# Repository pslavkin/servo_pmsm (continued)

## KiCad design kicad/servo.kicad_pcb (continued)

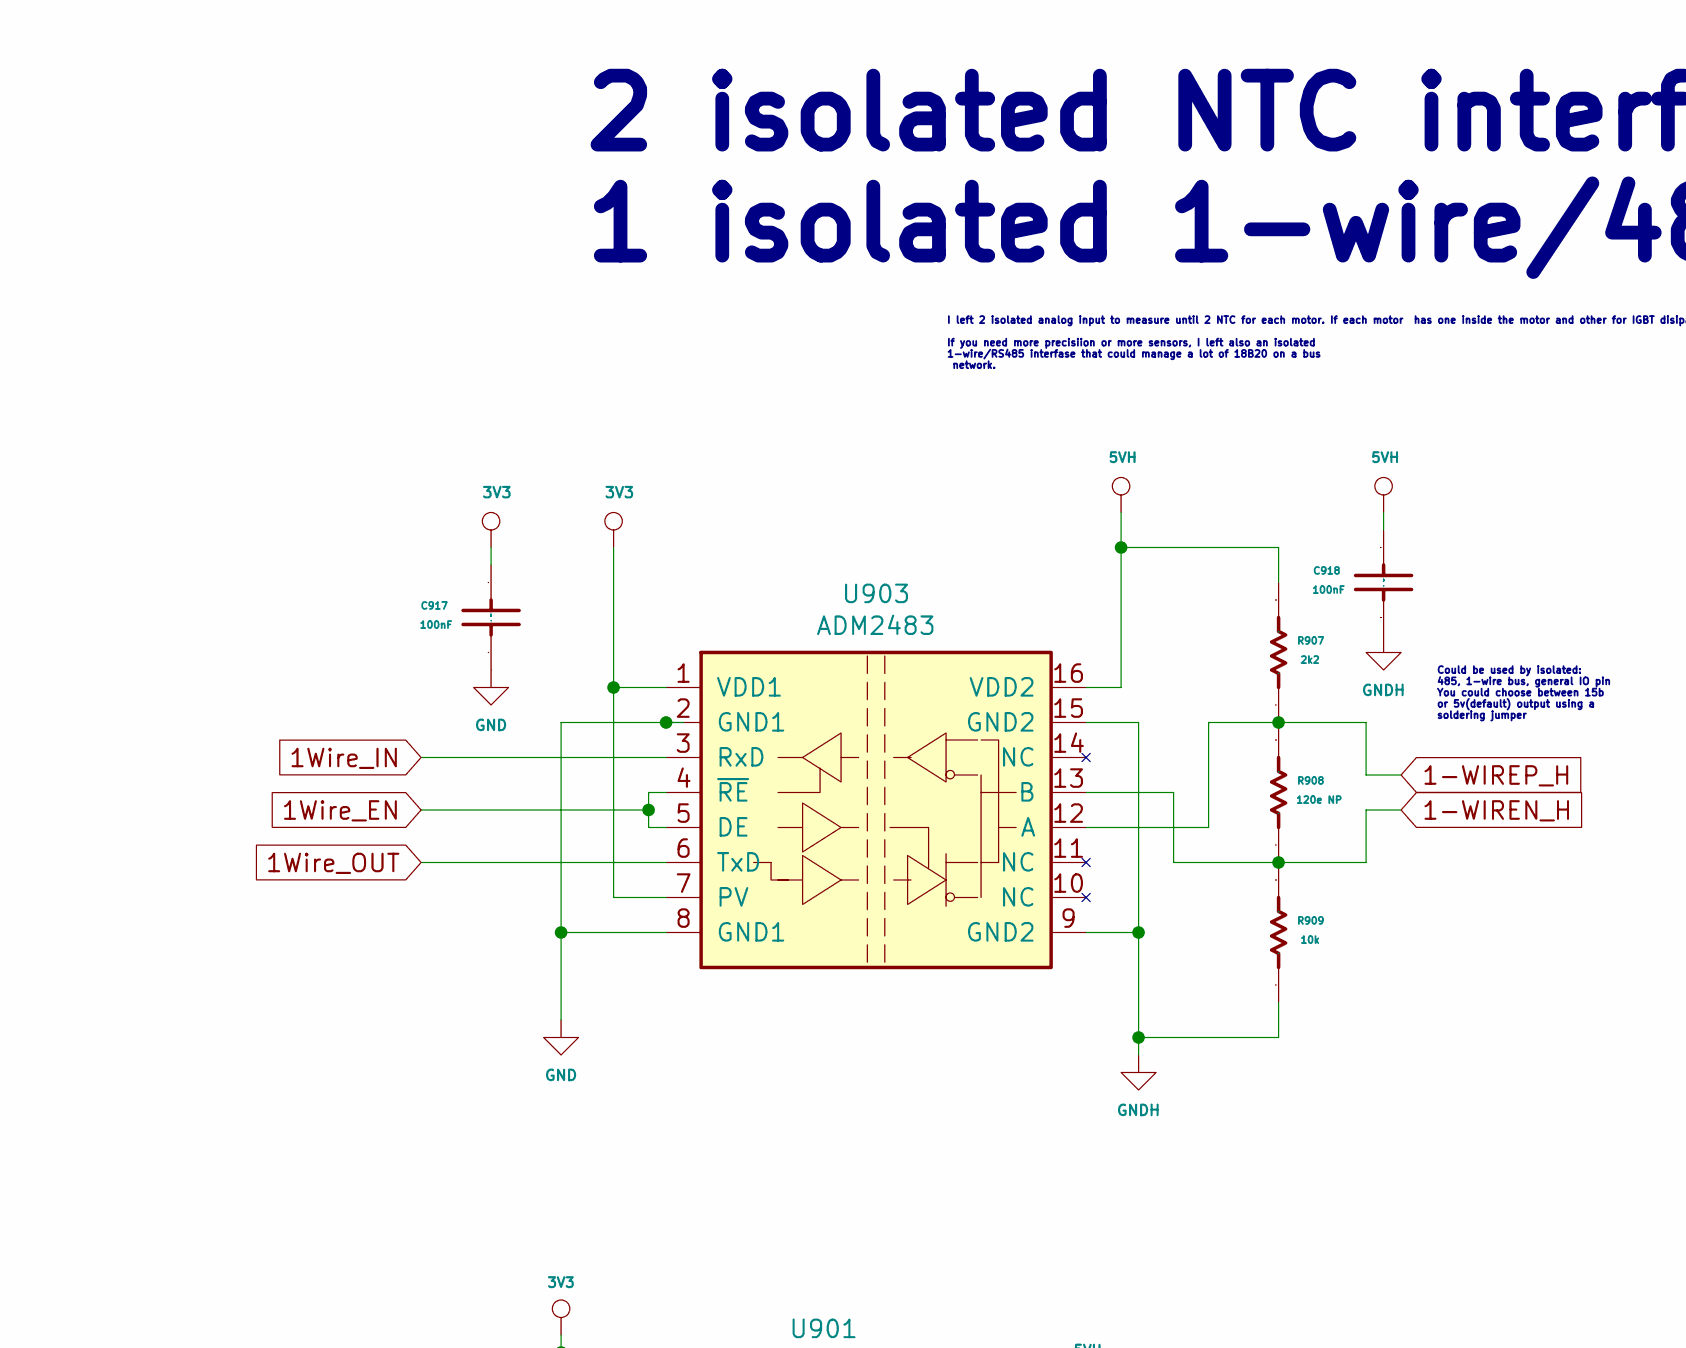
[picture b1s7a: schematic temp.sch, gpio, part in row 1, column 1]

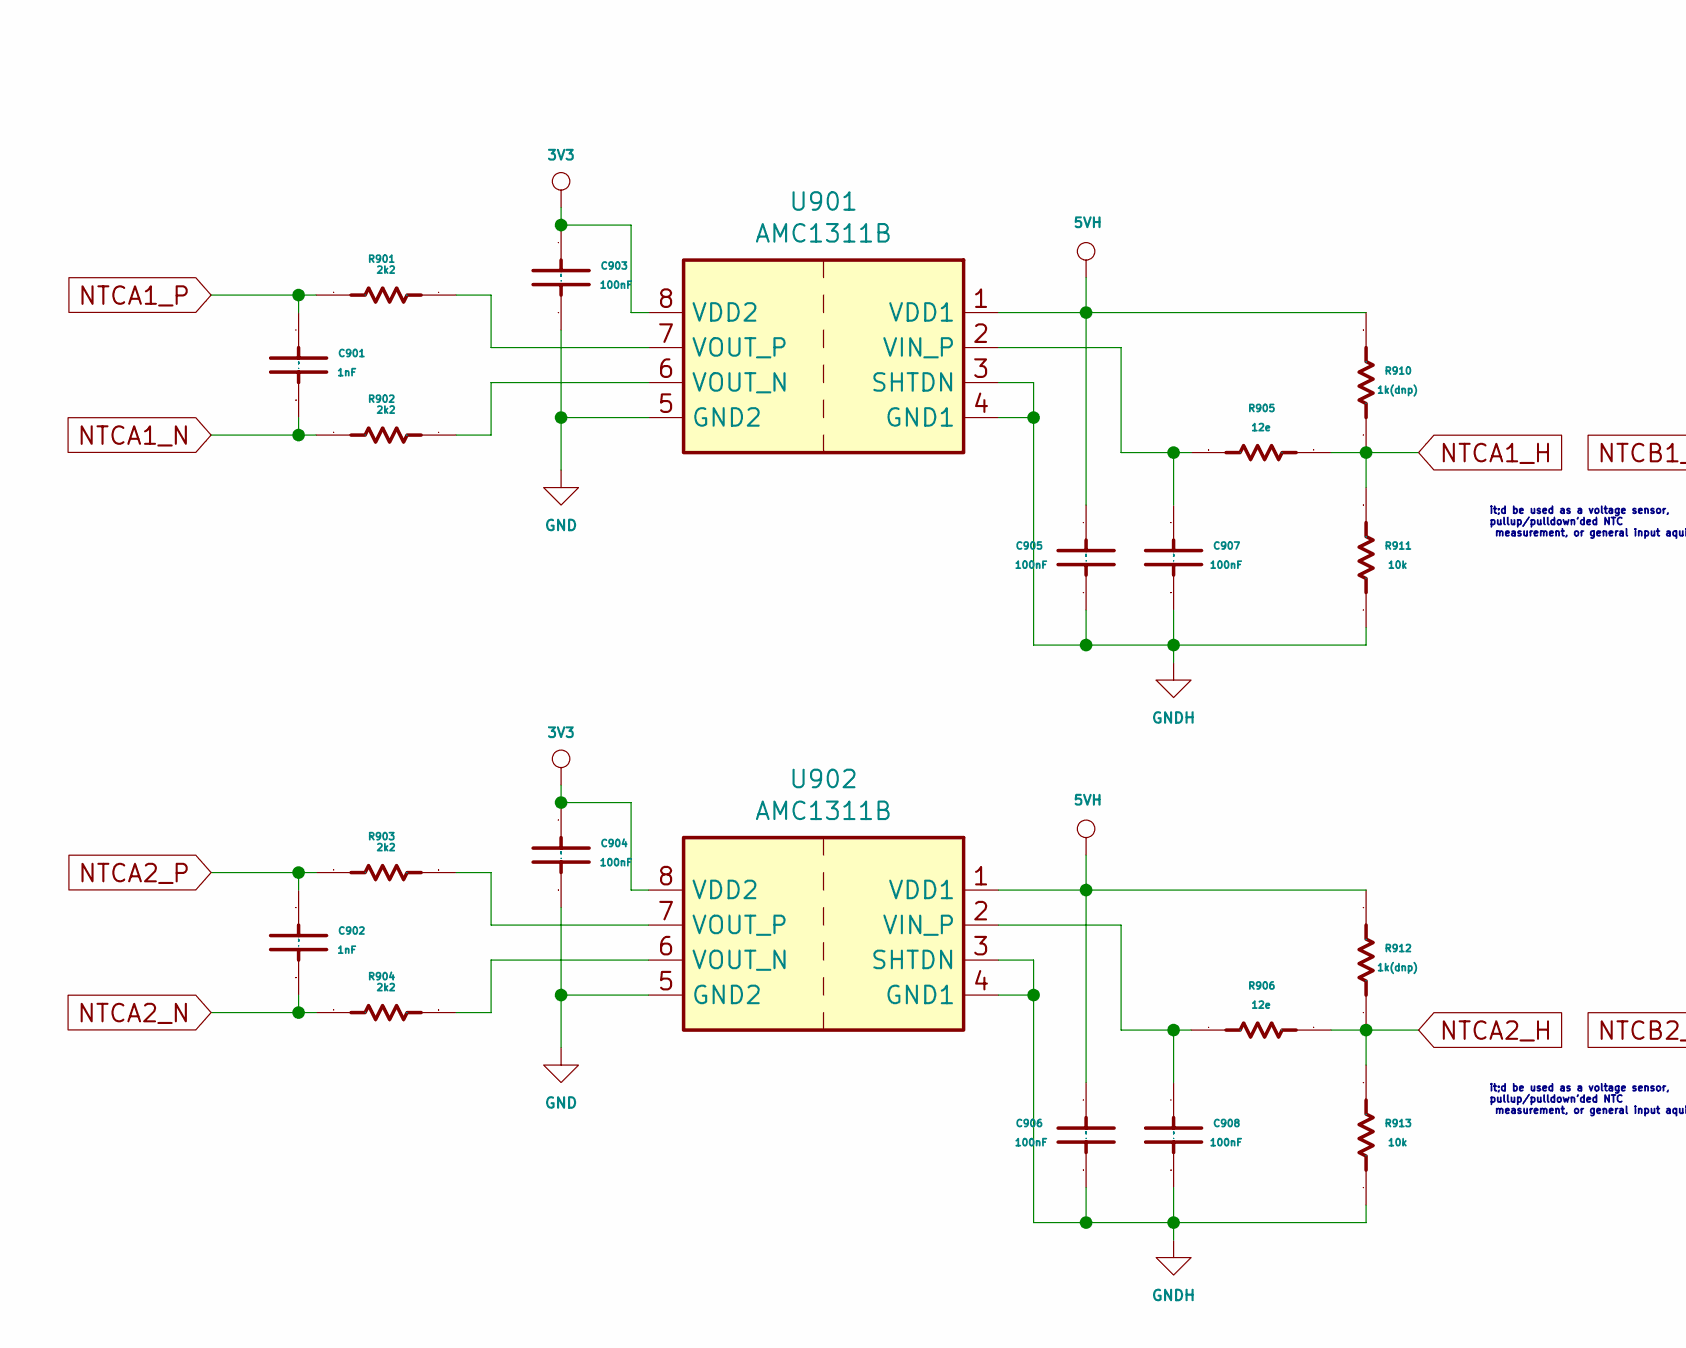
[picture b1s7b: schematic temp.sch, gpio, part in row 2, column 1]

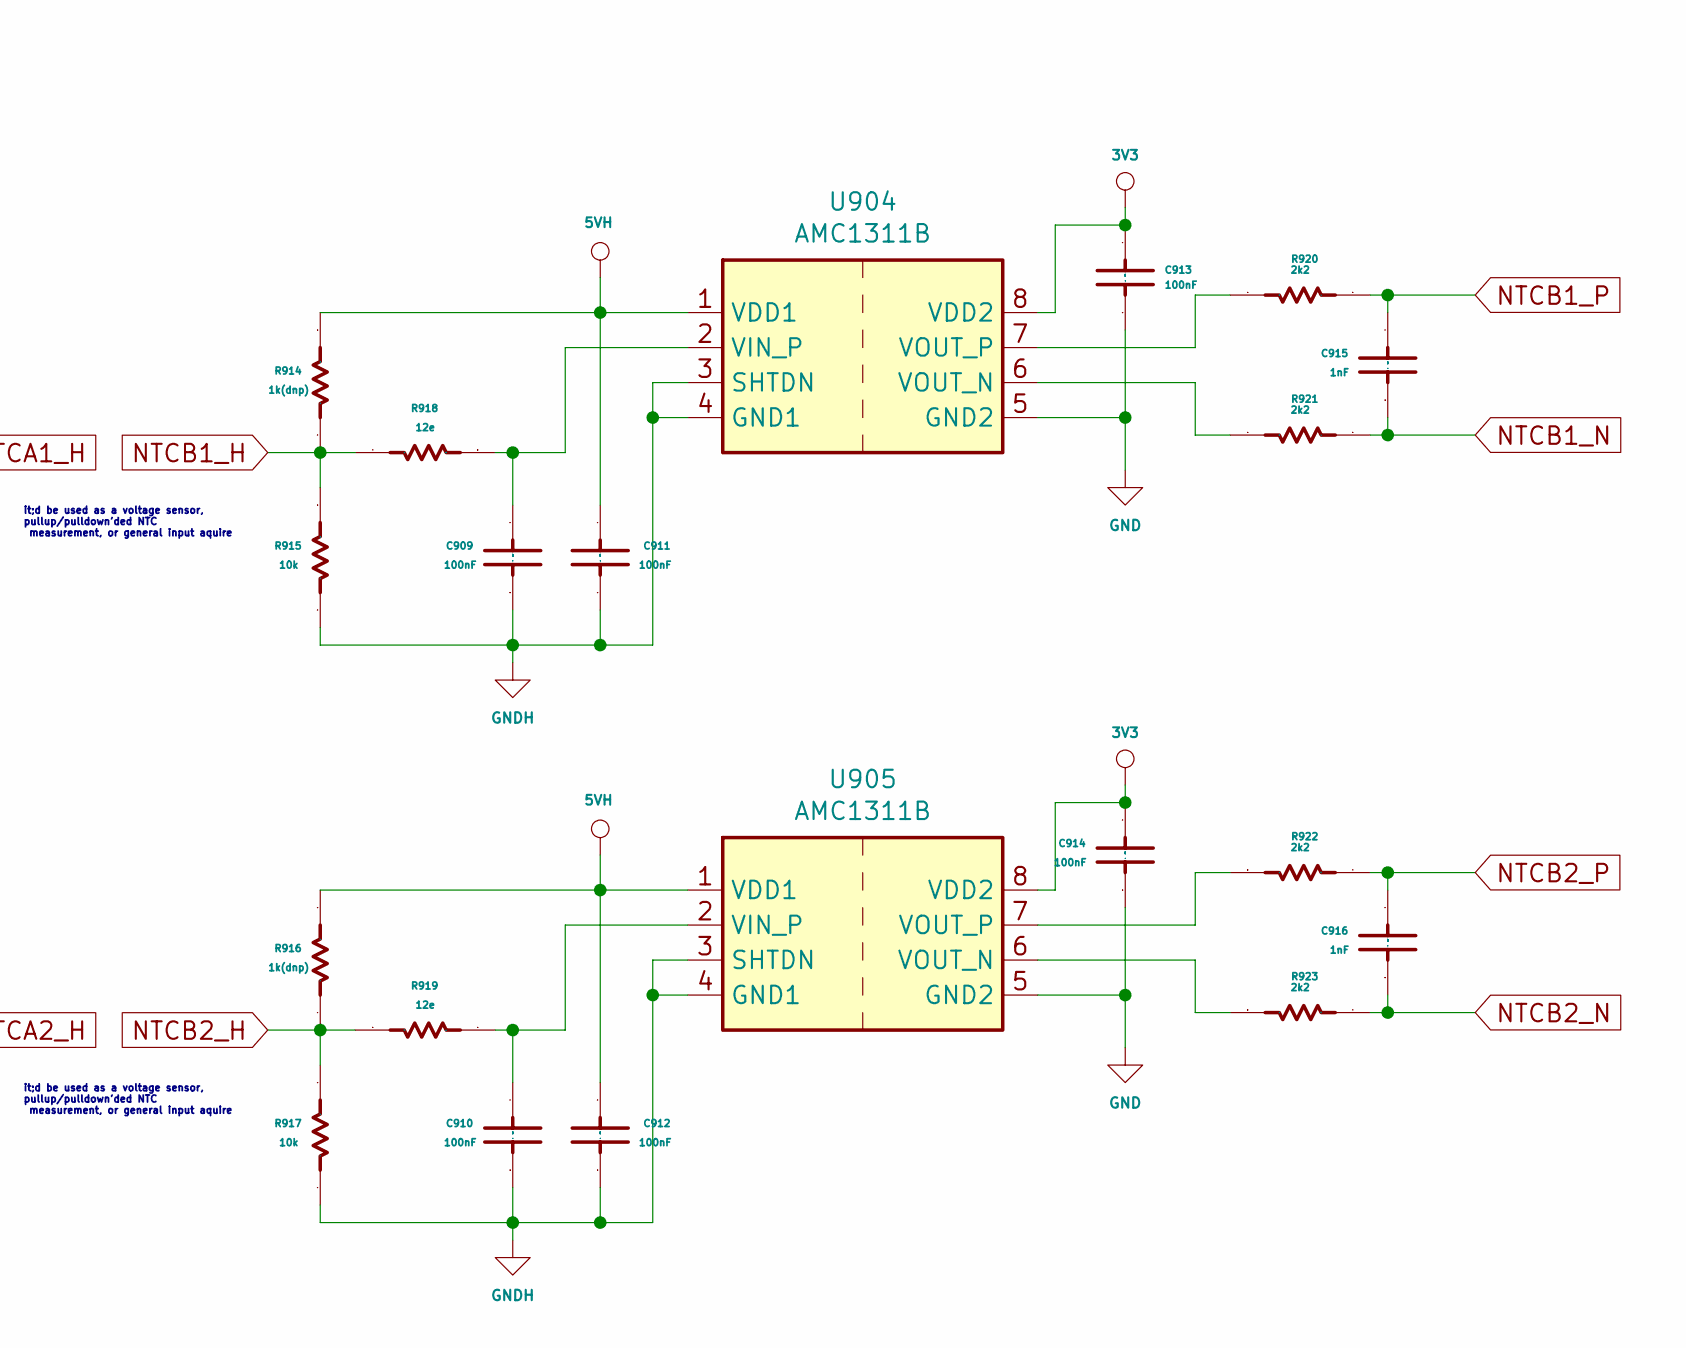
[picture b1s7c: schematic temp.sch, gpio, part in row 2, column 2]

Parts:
C901, C902, C915, C916: 1nF; C_0603_1608Metric
C903, C904, C905, C906, C907, C908, C909, C910, C911, C912, C913, C914, C917, C918: 100nF; C_0603_1608Metric
R901, R902, R903, R904, R907, R920, R921, R922, R923: 2k2; R_0603_1608Metric
R905, R906, R918, R919: 12e; R_0603_1608Metric
R908: 120e NP; R_0603_1608Metric
R909, R911, R913, R915, R917: 10k; R_0603_1608Metric
R910, R912, R914, R916: 1k(dnp); R_0603_1608Metric
U901, U902, U904, U905: AMC1311B; SSO-8_9.6x6.3mm_P1.27mm_Clearance10.5mm
U903: ADM2483; SOIC-16W_7.5x10.3mm_P1.27mm

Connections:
1-WIREN_H: R908.2, R909.1, U903.13 (B); also elsewhere on the board
1-WIREP_H: R907.2, R908.1, U903.12 (A); also elsewhere on the board
1Wire_EN: U903.4 (~RE), U903.5 (DE); also elsewhere on the board
1Wire_IN: U903.3 (RxD); also elsewhere on the board
1Wire_OUT: U903.6 (TxD); also elsewhere on the board
3V3: C903.2 (Capacitor), C904.2 (Capacitor), C913.2 (Capacitor), C914.2 (Capacitor), C917.2 (Capacitor), U901.8 (VDD2), U902.8 (VDD2), U903.1 (VDD1), U903.7 (PV), U904.8 (VDD2), U905.8 (VDD2); also elsewhere on the board
5VH: C905.2 (Capacitor), C906.2 (Capacitor), C911.2 (Capacitor), C912.2 (Capacitor), C918.2 (Capacitor), R907.1, R910.1, R912.1, R914.1, R916.1, U901.1 (VDD1), U902.1 (VDD1), U903.16 (VDD2), U904.1 (VDD1), U905.1 (VDD1); also elsewhere on the board
GND: C903.1, C904.1, C913.1, C914.1, C917.1, U901.5 (GND2), U902.5 (GND2), U903.2 (GND1), U903.8 (GND1), U904.5 (GND2), U905.5 (GND2); also elsewhere on the board
GNDH: C905.1, C906.1, C907.1, C908.1, C909.1, C910.1, C911.1, C912.1, C918.1, R909.2, R911.2, R913.2, R915.2, R917.2, U901.3 (SHTDN), U901.4 (GND1), U902.3 (SHTDN), U902.4 (GND1), U903.9 (GND2), U903.15 (GND2), U904.3 (SHTDN), U904.4 (GND1), U905.3 (SHTDN), U905.4 (GND1); also elsewhere on the board
NTCA1_H: R905.2, R910.2, R911.1; also elsewhere on the board
NTCA1_N: C901.1, R902.2; also elsewhere on the board
NTCA1_P: C901.2 (Capacitor), R901.2; also elsewhere on the board
NTCA2_H: R906.2, R912.2, R913.1; also elsewhere on the board
NTCA2_N: C902.1, R904.2; also elsewhere on the board
NTCA2_P: C902.2 (Capacitor), R903.2; also elsewhere on the board
NTCB1_H: R914.2, R915.1, R918.2; also elsewhere on the board
NTCB1_N: C915.1, R921.2; also elsewhere on the board
NTCB1_P: C915.2 (Capacitor), R920.2; also elsewhere on the board
NTCB2_H: R916.2, R917.1, R919.2; also elsewhere on the board
NTCB2_N: C916.1, R923.2; also elsewhere on the board
NTCB2_P: C916.2 (Capacitor), R922.2; also elsewhere on the board
unnamed: C907.2 (Capacitor), R905.1, U901.2 (VIN_P)
unnamed: C908.2 (Capacitor), R906.1, U902.2 (VIN_P)
unnamed: C909.2 (Capacitor), R918.1, U904.2 (VIN_P)
unnamed: C910.2 (Capacitor), R919.1, U905.2 (VIN_P)
unnamed: R901.1, U901.7 (VOUT_P)
unnamed: R902.1, U901.6 (VOUT_N)
unnamed: R903.1, U902.7 (VOUT_P)
unnamed: R904.1, U902.6 (VOUT_N)
unnamed: R920.1, U904.7 (VOUT_P)
unnamed: R921.1, U904.6 (VOUT_N)
unnamed: R922.1, U905.7 (VOUT_P)
unnamed: R923.1, U905.6 (VOUT_N)

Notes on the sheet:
Could be used by isolated: 485, 1-wire bus, general IO pin You could choose between 15b or 5v(default) output using a soldering jumper
2 isolated NTC interfase + 1 isolated 1-wire/485
it;d be used as a voltage sensor, pullup/pulldown'ded NTC measurement, or general input aquire
I left 2 isolated analog input to measure until 2 NTC for each motor. If each motor has one inside the motor and other for IGBT disipator, If you need more precisiion or more sensors, I left also an isolated 1-wire/RS485 interfase that could manage a lot of 18B20 on a bus network.

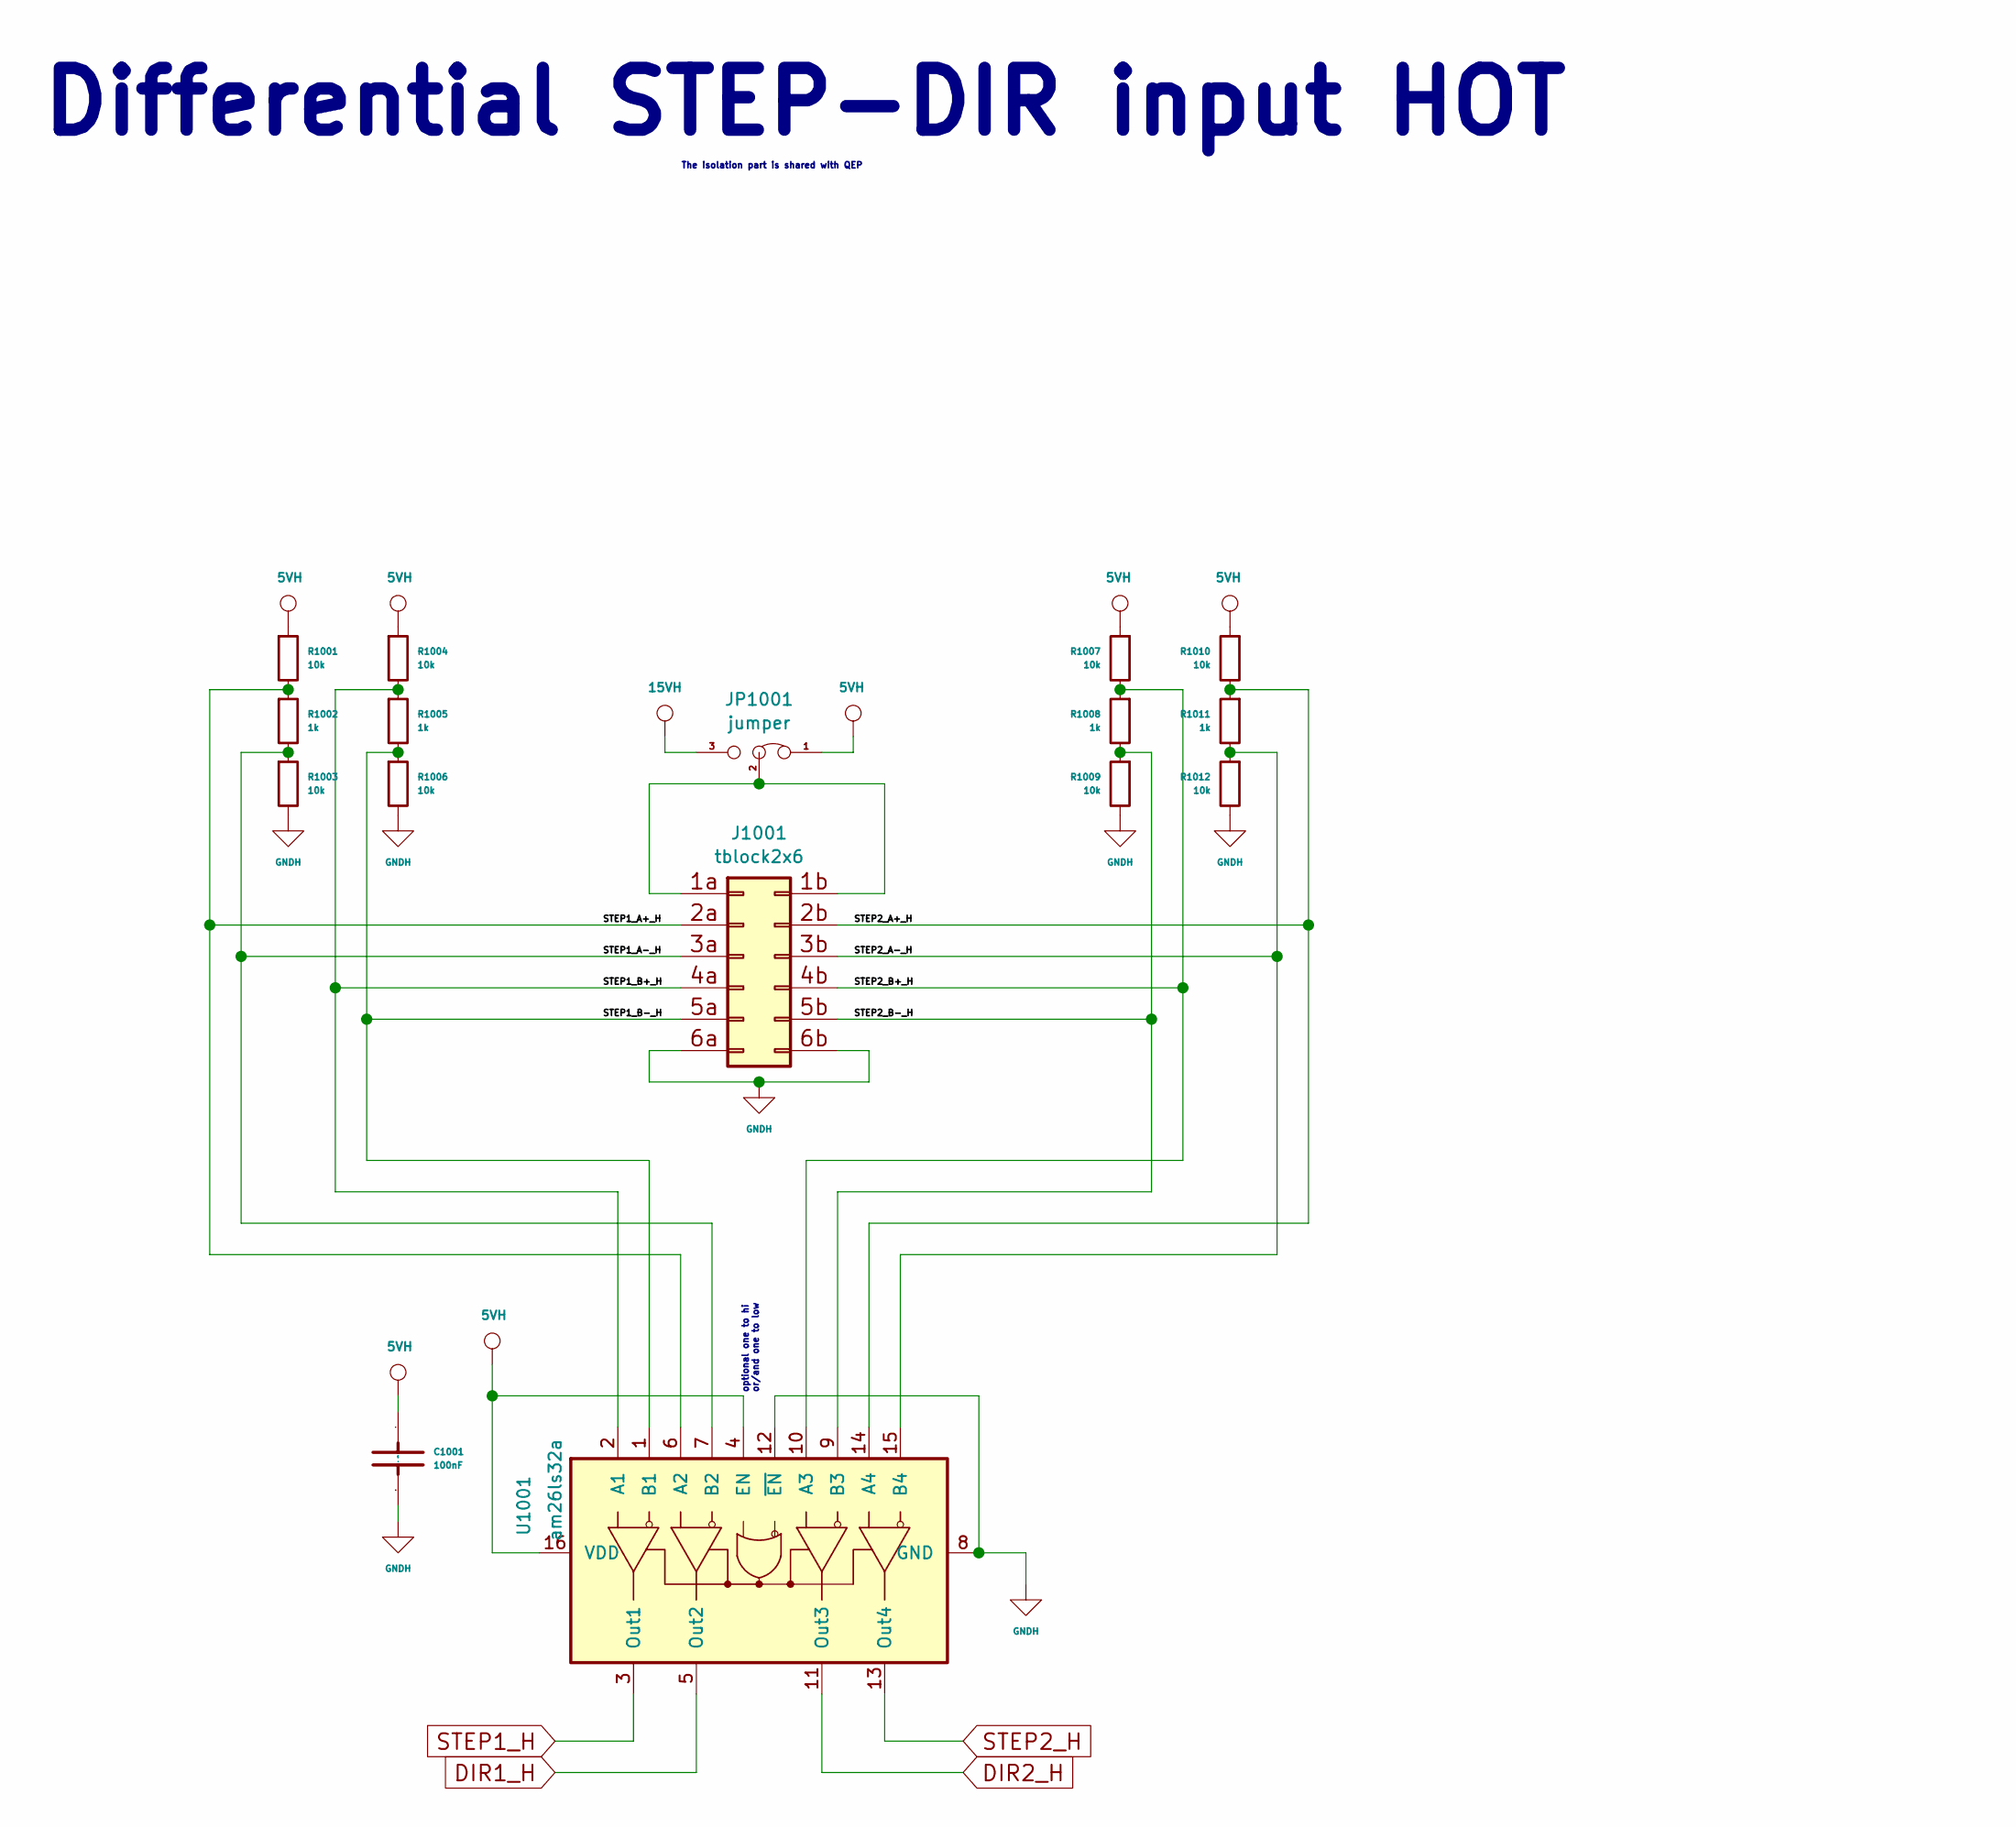
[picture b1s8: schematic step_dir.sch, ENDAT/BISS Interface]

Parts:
C1001: 100nF; C_0603_1608Metric
J1001: tblock2x6; tblock02x6_3.81
JP1001: jumper; SolderJumper-3_P1.3mm_Open_RoundedPad1.0x1.5mm
R1001, R1003, R1004, R1006, R1007, R1009, R1010, R1012: 10k; R_0603_1608Metric
R1002, R1005, R1008, R1011: 1k; R_0603_1608Metric
U1001: am26ls32a; SOIC-16W_5.3x10.2mm_P1.27mm

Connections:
5VH: C1001.2 (Capacitor), JP1001.1 (A), R1001.1, R1004.1, R1007.1, R1010.1, U1001.4 (EN), U1001.16 (VDD); also elsewhere on the board
15VH: JP1001.3 (B); also elsewhere on the board
/step_dir/STEP1_A+_H: J1001.2a, R1001.2, R1002.1, U1001.6 (A2)
/step_dir/STEP1_A-_H: J1001.3a, R1002.2, R1003.1, U1001.7 (B2)
/step_dir/STEP1_B+_H: J1001.4a, R1004.2, R1005.1, U1001.2 (A1)
/step_dir/STEP1_B-_H: J1001.5a, R1005.2, R1006.1, U1001.1 (B1)
/step_dir/STEP2_A+_H: J1001.2b, R1010.2, R1011.1, U1001.14 (A4)
/step_dir/STEP2_A-_H: J1001.3b, R1011.2, R1012.1, U1001.15 (B4)
/step_dir/STEP2_B+_H: J1001.4b, R1007.2, R1008.1, U1001.10 (A3)
/step_dir/STEP2_B-_H: J1001.5b, R1008.2, R1009.1, U1001.9 (B3)
DIR1_H: U1001.5 (Out2); also elsewhere on the board
DIR2_H: U1001.11 (Out3); also elsewhere on the board
GNDH: C1001.1, J1001.6a, J1001.6b, R1003.2, R1006.2, R1009.2, R1012.2, U1001.8 (GND), U1001.12 (~EN); also elsewhere on the board
unnamed: J1001.1a, J1001.1b, JP1001.2 (C)
STEP1_H: U1001.3 (Out1); also elsewhere on the board
STEP2_H: U1001.13 (Out4); also elsewhere on the board

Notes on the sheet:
Differential STEP-DIR input HOT
optional one to hi or/and one to low
The isolation part is shared with QEP

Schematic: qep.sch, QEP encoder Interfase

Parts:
C1101, C1102, C1103, C1104, C1105, C1106: 100nF; C_0603_1608Metric
J1101: tblock; tblock02x10_3.81
JP1101: jumper; SolderJumper-3_P1.3mm_Open_RoundedPad1.0x1.5mm
R1101, R1103, R1104, R1106, R1107, R1109, R1110, R1112, R1113, R1115, R1116, R1118, R1119, R1121, R1122, R1124: 10k; R_0603_1608Metric
R1102, R1105, R1108, R1111, R1114, R1117, R1120, R1123: 1k; R_0603_1608Metric
U1101, U1104: SI8660BD; SOIC-16W_7.5x10.3mm_P1.27mm
U1102, U1103: am26ls32a; SOIC-16W_5.3x10.2mm_P1.27mm

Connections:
3V3: C1101.2 (Capacitor), C1106.2 (Capacitor), U1101.16 (VCC2), U1104.16 (VCC2); also elsewhere on the board
5VH: C1102.2 (Capacitor), C1103.2 (Capacitor), C1104.2 (Capacitor), C1105.2 (Capacitor), JP1101.1 (A), R1101.1, R1104.1, R1107.1, R1110.1, R1113.1, R1116.1, R1119.1, R1122.1, U1101.1 (VCC1), U1102.4 (EN), U1102.16 (VDD), U1103.4 (EN), U1103.16 (VDD), U1104.1 (VCC1); also elsewhere on the board
15VH: JP1101.3 (B); also elsewhere on the board
/qep/QEP1_A+_H: J1101.2a, R1101.2, R1102.1, U1102.2 (A1)
/qep/QEP1_A-_H: J1101.3a, R1102.2, R1103.1, U1102.1 (B1)
/qep/QEP1_B+_H: J1101.4a, R1104.2, R1105.1, U1102.6 (A2)
/qep/QEP1_B-_H: J1101.5a, R1105.2, R1106.1, U1102.7 (B2)
/qep/QEP1_I+_H: J1101.6a, R1107.2, R1108.1, U1102.10 (A3)
/qep/QEP1_I-_H: J1101.7a, R1108.2, R1109.1, U1102.9 (B3)
/qep/QEP1_S+_H: J1101.8a, R1110.2, R1111.1, U1102.14 (A4)
/qep/QEP1_S-_H: J1101.9a, R1111.2, R1112.1, U1102.15 (B4)
/qep/QEP2_A+_H: J1101.2b, R1122.2, R1123.1, U1103.2 (A1)
/qep/QEP2_A-_H: J1101.3b, R1123.2, R1124.1, U1103.1 (B1)
/qep/QEP2_B+_H: J1101.4b, R1119.2, R1120.1, U1103.6 (A2)
/qep/QEP2_B-_H: J1101.5b, R1120.2, R1121.1, U1103.7 (B2)
/qep/QEP2_I+_H: J1101.6b, R1116.2, R1117.1, U1103.10 (A3)
/qep/QEP2_I-_H: J1101.7b, R1117.2, R1118.1, U1103.9 (B3)
/qep/QEP2_S+_H: J1101.8b, R1113.2, R1114.1, U1103.14 (A4)
/qep/QEP2_S-_H: J1101.9b, R1114.2, R1115.1, U1103.15 (B4)
DIR1: U1101.10 (B6); also elsewhere on the board
DIR1_H: U1101.7 (A6); also elsewhere on the board
DIR2: U1104.10 (B6); also elsewhere on the board
DIR2_H: U1104.7 (A6); also elsewhere on the board
GND: C1101.1, C1106.1, U1101.9 (GND2), U1104.9 (GND2); also elsewhere on the board
GNDH: C1102.1, C1103.1, C1104.1, C1105.1, J1101.10a, J1101.10b, R1103.2, R1106.2, R1109.2, R1112.2, R1115.2, R1118.2, R1121.2, R1124.2, U1101.8 (GND1), U1102.8 (GND), U1102.12 (~EN), U1103.8 (GND), U1103.12 (~EN), U1104.8 (GND1); also elsewhere on the board
unnamed: J1101.1a, J1101.1b, JP1101.2 (C)
unnamed: U1101.2 (A1), U1102.3 (Out1)
unnamed: U1101.3 (A2), U1102.5 (Out2)
unnamed: U1101.4 (A3), U1102.11 (Out3)
unnamed: U1101.5 (A4), U1102.13 (Out4)
unnamed: U1103.3 (Out1), U1104.2 (A1)
unnamed: U1103.5 (Out2), U1104.3 (A2)
unnamed: U1103.11 (Out3), U1104.4 (A3)
unnamed: U1103.13 (Out4), U1104.5 (A4)
QEP1_A: U1101.15 (B1); also elsewhere on the board
QEP1_B: U1101.14 (B2); also elsewhere on the board
QEP1_I: U1101.13 (B3); also elsewhere on the board
QEP1_S: U1101.12 (B4); also elsewhere on the board
QEP2_A: U1104.15 (B1); also elsewhere on the board
QEP2_B: U1104.14 (B2); also elsewhere on the board
QEP2_I: U1104.13 (B3); also elsewhere on the board
QEP2_S: U1104.12 (B4); also elsewhere on the board
STEP1: U1101.11 (B5); also elsewhere on the board
STEP1_H: U1101.6 (A5); also elsewhere on the board
STEP2: U1104.11 (B5); also elsewhere on the board
STEP2_H: U1104.6 (A5); also elsewhere on the board

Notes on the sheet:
2x Isolated Idifferential ncremental encoder interfase 5v input A-B-I-S
I left the input for two isolated incremental encoders. I left the 4 signals input plus two auxiliary output for eny porpous plus the ability to choose between 5 or 15vH
optional one to hi or/and one to low
Choose a package pin-to-pin compatible with TI ISO7760. But SIlabs cost halt the price as TI

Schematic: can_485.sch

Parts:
C1201, C1202, C1203, C1204: 100nF; C_0603_1608Metric
J1201: tblock2x4; tblock02x4_3.81
JP1201, JP1202: jumper; SolderJumper-3_P1.3mm_Open_RoundedPad1.0x1.5mm
R1201, R1203, R1204, R1206: 10k; R_0603_1608Metric
R1202, R1205: 1k; R_0603_1608Metric
U1201: ISO1050; SSO-8_6.7x9.8mm_P2.54mm_Clearance8mm
U1202: ADM2483; SOIC-16W_7.5x10.3mm_P1.27mm

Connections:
3V3: C1201.2 (Capacitor), C1204.2 (Capacitor), U1201.1 (VCC1), U1202.1 (VDD1), U1202.7 (PV); also elsewhere on the board
5VH: C1202.2 (Capacitor), C1203.2 (Capacitor), JP1201.1 (A), R1201.1, R1204.1, U1201.8 (VCC2), U1202.16 (VDD2); also elsewhere on the board
15VH: JP1201.3 (B); also elsewhere on the board
CAN_RX: U1201.2 (RxD); also elsewhere on the board
CAN_TX: U1201.3 (TxD); also elsewhere on the board
Earth: JP1202.1 (A); also elsewhere on the board
GND: C1201.1, C1204.1, U1201.4 (GND1), U1202.2 (GND1), U1202.8 (GND1); also elsewhere on the board
GNDH: C1202.1, C1203.1, JP1202.3 (B), R1203.2, R1206.2, U1201.5 (GND2), U1202.9 (GND2), U1202.15 (GND2); also elsewhere on the board
unnamed: J1201.1a, J1201.1b, JP1201.2 (C)
unnamed: J1201.2a, R1201.2, R1202.1, U1201.7 (CANH)
unnamed: J1201.2b, R1204.2, R1205.1, U1202.12 (A)
unnamed: J1201.3a, R1202.2, R1203.1, U1201.6 (CANL)
unnamed: J1201.3b, R1205.2, R1206.1, U1202.13 (B)
unnamed: J1201.4a, J1201.4b, JP1202.2 (C)
RS485_EN: U1202.4 (~RE), U1202.5 (DE); also elsewhere on the board
RS485_RX: U1202.3 (RxD); also elsewhere on the board
RS485_TX: U1202.6 (TxD); also elsewhere on the board

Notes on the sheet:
Isolated CAN interfase
A simple CAN driver. It also could be used as a RS485 driver in his speed.. the minimum for CAN is 40kbos, so in RS485 at 9600 could be fine
Could be used by isolated: 485, 1-wire bus, general IO pin
Isolated RS485
With these interfase you could manage isolated RS485 or isolated GPIO or isolated 1-Wire, using 5H or 15H as a supply

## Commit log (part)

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2019-07-05 biginig. do comppile, do run on cpi, all code on git
    I spend a couple of days understunding the c2000 driverlib arquitecture
    to manage my own project workspace all incluede. I only depends on the
    compiler, but the fp32.lib, and driverlib codes, and header are all
    inside the gir, so I'd change everythins and move the project from PC
    without looss codes.. let go!
2019-07-05 blow up 'cose project name change. Solved -> servo_pmsm
2019-07-06 cbuffers into scia. as a module, so I'd use cbuffer for events
2019-07-06 leds up! lets ticl begore the parser...
    I've added some files to git, that I'd forget from last commit.. leds
    are running and ready to use. I'm planning the tick begore parsser..
2019-07-07 systick with flag UP!, the problem is related to isr chained
    I remove the enable/disable isr for timer2 when in smachine and the
    problem of jitter goes. It seems that timer2 doesn't like it. I decided
    for now add at the end of sm a systick function that pool a flag that
    timer2 isr set. So I don't need to disable/enable irqs to read the
    events, 'cose til now the event writes are done allways in user mode,
    not isr.. but it could change latter..
2019-07-08 uptime print UP!, just to test the cmdlineProcces
    I've added a simple clock to check the uptime and see if the systems got
    hangs suddenly... keep working
2019-07-09 ADC UP! using SOC and software trigger 12bits single ended
    I've manage to put adc to work configurin 12bits using soc0 and testing
    irq flag to test completion. It's basic but working example integrated
    ti the rtos and cmdline to sample using sci and keyboard, si it's ready
    to modify, go on...
2019-07-11 keep doing README adding requisites
2019-07-11 added gif video demo for sci test and some updates in README
2019-07-11 test scaled gif for readable solution
2019-07-13 add iqmath lib for eqep.c calculations. Also change cmd's
    I've added eqep, but it need iqmath lib, so I'd to add thouse .libs and
    .h include files to manage that. Not Debug and Release versions works, o
    at least compile and don't hang. Now it's time to test eqep output..
    lets go
2019-07-14 EQEP at 50kedges/sec works. Maybe it's hardware limitation
    I'm measuring speed of 50kedges/sec max. I guess the pulse deformation
    and the 5v<->3v translator limitation could distor the pulses. I'll
    measure next by osc. For now it's enought to continue with the
    calculations.
2019-07-15 motor encoder interface UP! see the video demo
    I've tested the encoder of the motor connected to the interface
    implemented, and it worked as expected, see the video on README.md, so
    next I'll begin with 3phase PWM, let see
2019-07-18 BLUE BOARD SPIN UP! first try and motor do spin, hardw is OK!
    first spin using the blue board, hardware seems ok, at least the part of
    it that participate in the run. I'm planning to mix the launchpad dev
    with controlboard design to be in the best of two worlds. let see
2019-07-23 Beginig the porting from launchpad -> controlBoard, it works!
    I've port the project simply by undefined the LAUNC macro, and modifying
    the make scripts, and it works. So I'am adding some code from demo to my
    actual RTOS in the corresponding module, not in a plain file, and I'll
    test step by step each of them to understand the whole things.
2019-08-10 I've closed the current loop in tyos, testing
    I've closed the loop using the pwm interrupt to aquire adc and make the
    calculations ipark and so, and also the mechanic position. so naw the
    pwm follow the mechanical position , but I've somo isue with limiting
    the current, i doesnt' track idref in small values. I'm investigating it
2019-08-27 start your engines.. in moldova motors are spinning
    I'd maage to spin two incremental encoders servomotors and play a little
    with them. I'm trying to recognize the real requeriments for the master
    plan project.
2019-08-29 cleaning example to buildlevel5 only
2019-08-30 break apart example ever think on it's own module
    I'm having troubles with quep, couse everything is mixed up, but i'll
    try again
2019-08-30 keep cleaning more.. and stay working code
2019-08-31 aproach pointer to funcion, first testings work...
2019-08-31 just erasing code everywere to got the juice
2019-09-02 serial log with gnuplot works!
    I've added a gnuplot dir with some scripts and read a log file.
    I've also recompiled picocom with file log features and with thouse I've
    plotting data on realtime very well, now I'm planing to choose when to
    log and to change pid parameters on runtime..
2019-09-03 added state machin in fcl to start in step and manage overcurrent
    I'm adding states in fcl to manage more situations like stop run,
    overcurrent and so.. it;s runnung partiali..
2019-09-04 stop/run in fcl work soso, sincgenerator works better
    I fix som issues in sinc generator and it got better and now you can
    make a sin in any abs place, becosu it has a center option.
2019-09-05 step generator works, and also qep simulation
    I've made the step generator works and it's great for testing overshoot
    and eveything time performance analisis. I;ve added a qep simulator to
    test generator things without motor moviments.. keeps going..
2019-09-06 working on accelerate-constatn-decelerate function
    it's working just for one side
2019-09-06 gcode is HERE!, and it work g0, F accel deccel
    it simpler, but it works and it's very useful
2019-09-07 add sender to automatice menu control
    I've adde some scripting to automatice common use of the api, is in dev,
    but work fin. I'm seeing that it's dificult to follow the lines.. but
    I've to parametice PID
2019-09-09 step dir in ISR works!, now it can be tested using a controller
    I've added isr for step and irection, one rise/fall and the other only
    fall (it can be customized) and when the pulse is detected just
    increment the desired position on step ahead.
2019-09-14 swept break apart, log with pause and 4 poles test
    Added some README content also. I'm trying to solve the reinit problem
    without overcurren and/or a system reset
2019-09-18 added some pics/videos and readme stuff
    add some pics and videos related to the progress
2019-09-18 testing with CNC controller pulse/dir it works!!
    just work, now it's time to manaje the pulse to position conversion and
    the optocoupler waveform is destroyed, so we're trying to calibrate that
2019-09-19 last release in Moldova, minor changes
    I've flashed the last releast at moldova's labs. lets see next.
2019-10-12 gotcha park IQ by hand based on LemV/W what next?
    Ok, I've the clerk/park transformation correctly matching tecas FCL. Now
    it's time to calculat them on ISR and try to pass them throught a pid
    and controll it.. let see
2019-10-13 it's fine to add a huge mass at the motor and do equations
    let's add some mass and do equations and see if the model of R-L is
    enought
2019-10-16 finish cdi final tp, with 3 chained PID for pos control
2019-11-07 begin with PCB branch in orphan git method
2019-11-07 adc added but not checked yest.. i
    adc deserves a special attention becouse we don't want so much channels,
    nor differential input.. neither so much references..
2019-11-17 usb interface changed by emu_interface
    I've cleaned all the jtag interface, so the only things that go out is
    jtag HOT and rx/tx isolated. I left the isolator for rx/tx cose I'm
    planning to add rs485 using the same isolator and regulator, if not, I'd
    clean these IC's also
2019-11-18 added README pics, and keep going on power sch
    I've been deleting some unused IC's and accomodating libs, also add some
    pics to README
2019-11-22 cleaning power, added ac/dc to 15v
    I've added the ac/dc power supply based on encapsulated off load power
    supply and chainde linear regulator for 5, 3v3 and 1v2 for cold gnd and
    5v and 3v3 for hot gnd.
    I'll next join some sheet 'cose some of those are almost empty
2019-11-26 added igbt interface, lem, and impprove root page
    improved root page, added lem using hall sensor instead shunt, add
    somthing on adc page, and ac input.. keep working
2019-12-02 added shunt using sigma delta, just fot 1 channel
    I've added a sigma delta isolated sampler for use with shunt in phase
    measurement. 'cose it seems is the best accuracy method for current
    measurement, but it implies a lot of componentes, 8 PWM lines to
    generate the sigma delta clk, or maybe I'd use only one clk for all
    sigma deltas, ..I've to think about it, but it seems that should be
    better than Hall.. working on that
2019-12-02 typo fix on README
2019-12-26 Come back to moldova to finish schematics and begin layout
    I've started again from Moldova to discuss with Alexander the details.
    I'm now working with schematics requeriments.
2020-01-03 added buffers and leds 2 igbt. added xtal for PHY's
    I've added one xtal for each PYH instead/appart of the uC pin to drive
    the clk for thouse IC's. If the uC could manage to clk them, just
    depoppulate the xtal, if not, 3 xtal will be needed. But I guess is
    better than distribuiton of 25Mhz between IC's, even they were
    buffered...
2020-01-08 improve ethercat, embedded rj45 to spare, remove some unnecesary r's
    I've worked on ethetcat/net to improve visibility on A3 page and also
    remove some R's related to leds and change the embedded Rj45 for the
    spare transformer and connector 'cause half the price and more options
    to choose the connector shape and position
2020-01-09 added 4 push buttons and more gpios on LCD connector
    just to have more UI options. With those I'd manage graphics LCD plus 4
    buttons, and charaveter LCD. or the embedded EVE graphic LCD
2020-01-11 passed all footprint, preliminarly.. and taken a pic
    I've passed all 3d models, and make a pic of that, it's the first
    impresion, but it need's more indeed reviews
2020-01-14 added some 3d models, elminating 15vc and 2 lems
    I've elminated 15vc 'cause I don't use these voltage, so I'd change 20w
    15v heating power to 10w 5v more efficiency voltage to drive 3.3 and
    1.2v to the core and logic. I've also elminated 2 LEMS 'cause space..
    even thought there remain 3 for each motor.. more than necesary...keep
    going
2020-01-17 changed 200mils connector to 150mils 'cause space constraints
    I've decided to change 200 mils input connector for encat, rs485 and so
    for 150mis 'cose it doesn't deliver so much current and I'd save some
    space in the board. I've added the step/dir differential interface that
    I've fotgot, and also add differential input to all signals of
    incremental encoder interface A/B/I/S .. now lets rock
2020-01-20 All IC placed inside board size but....
    I've placed all stuff on board size even thought all are in groups I've
    to move the IC to route them. Let's begin
2020-01-22 beginine routing... far far away
2020-01-24 roouting and more routing.... I think 4 layers WONT be enought
2020-01-25 keep routing.....
2020-01-27 it's getting harder and harder
2020-01-30 add optional mounting case
2020-02-01 keep improving... added 2d and 3d nets pics
2020-02-03 added sloted holes everyware
2020-02-04 serigraphi, improve of nets. change of soic 8 footprint
2020-02-04 gerbers READY!!. leving Moldova..
    maybe the gerbers deserve a check, but at least they are ready..
    I'm leaving Moldova in two days.. and we will see..
2020-02-16 keep improving from Bariloche
2020-02-19 begining error checker on PCB
2020-02-25 more bom...
2020-03-03 changes in footprints
2020-03-04 fine imprivements
